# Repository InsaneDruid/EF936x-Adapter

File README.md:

# The EF936x-Adapter
Adapter for using an EF9367 instead of an EF9366/65, especially on the Low Speed Graphik graphics board

[Schematic](https://github.com/InsaneDruid/EF936x-Adapter/blob/main/ef936x_adapter.pdf "Schematic")  

[Bill of Materials](https://htmlpreview.github.io/?https://github.com/InsaneDruid/EF936x-Adapter/blob/main/bom/ef936x_adapter_bom.html "Bill of Materials")

## The License
This work is licensed under a Creative Commons Attribution-ShareAlike 4.0 International License.  
See https://creativecommons.org/licenses/by-sa/4.0/.

## The Credits
This work would not have been possible without the help from a bunch of amazing people from [VzEkC e. V. forums](https://forum.classic-computing.de/forum/ "forum.classic-computing.de"). Many thanks go out to:

* *AndyG* - for the images of the original hardware that were the inspiration and backbone for this project

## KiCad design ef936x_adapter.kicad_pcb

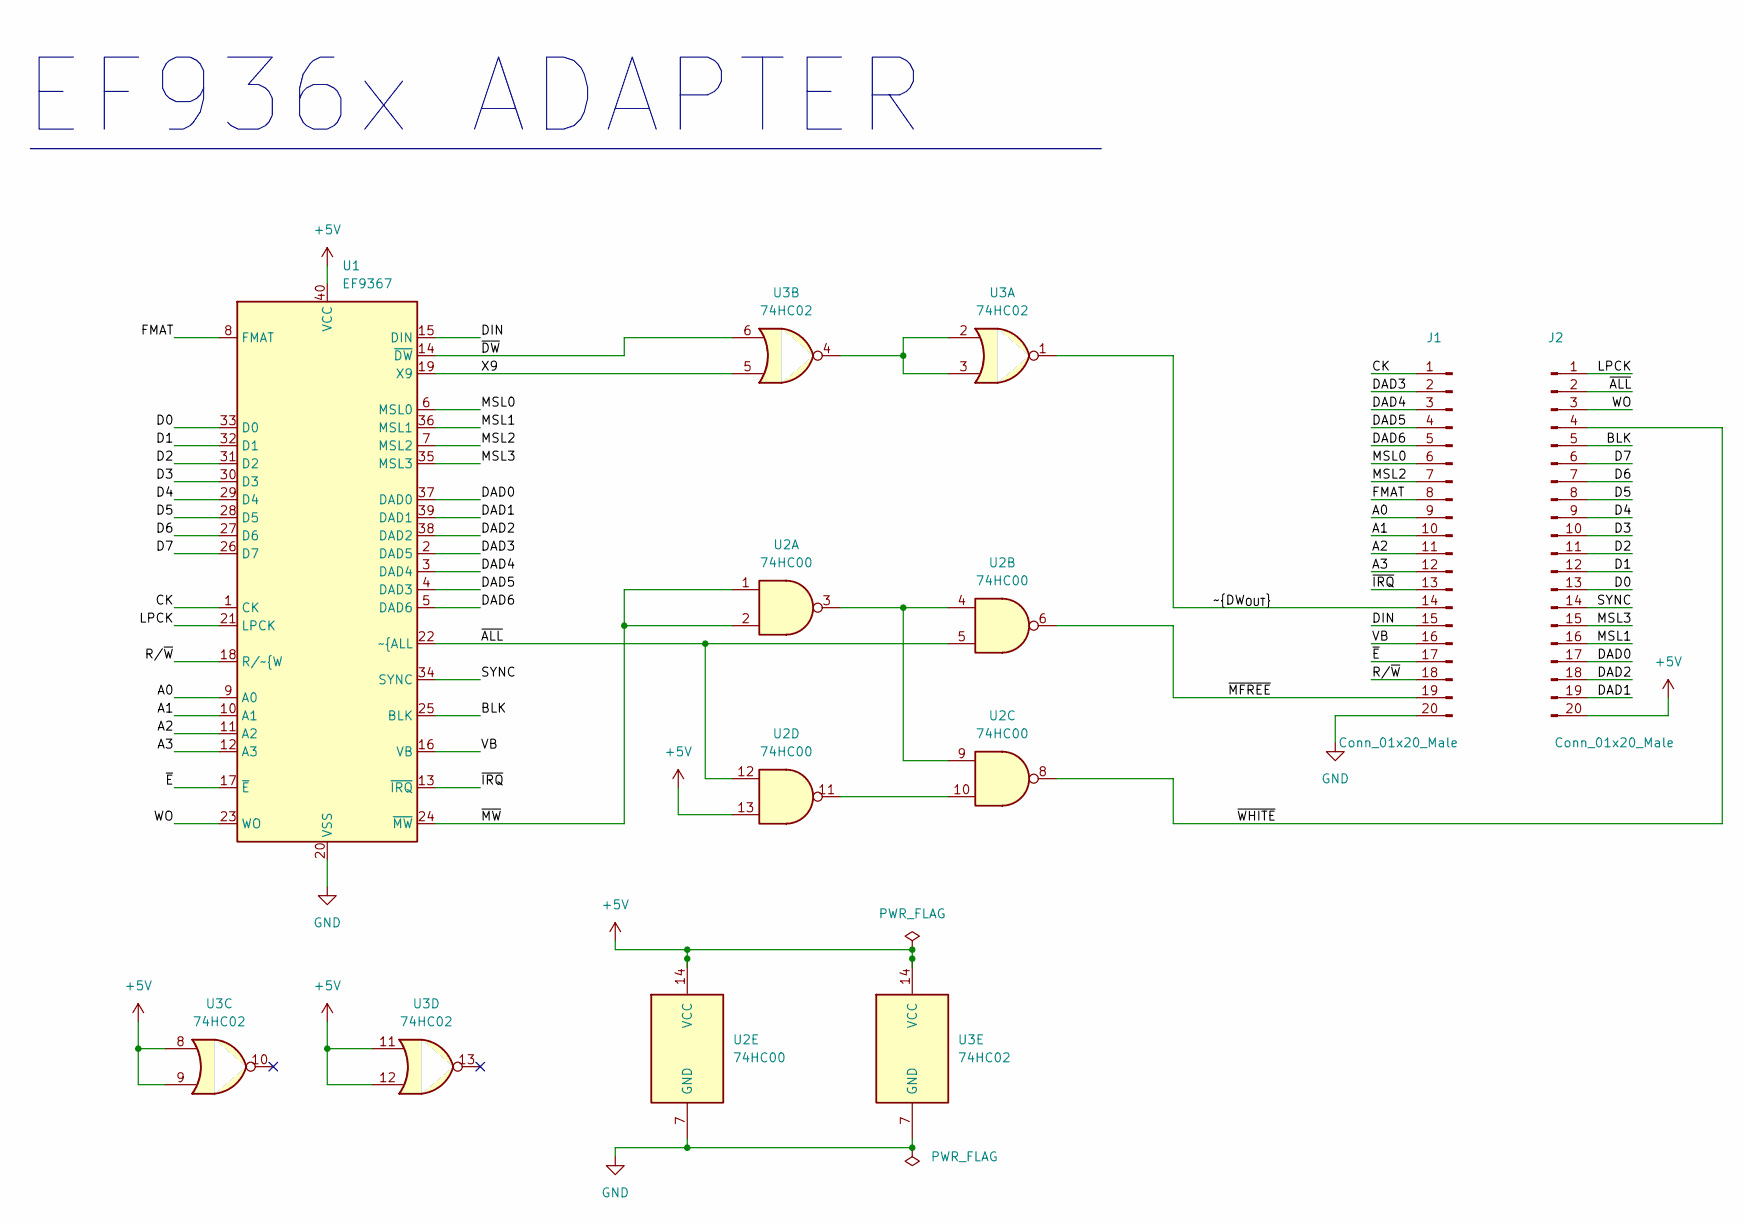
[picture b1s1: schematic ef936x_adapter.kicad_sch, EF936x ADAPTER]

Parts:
J1, J2: Conn_01x20_Male; PinHeader_1x20_P2.54mm_Vertical
U1: EF9367; DIP-40_W15.24mm_Socket
U2: 74HC00; DIP-14_W7.62mm
U3: 74HC02; DIP-14_W7.62mm

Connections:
+5V: J2.20, U1.40 (VCC), U2.13, U2.14 (VCC), U3.8, U3.9, U3.11, U3.12, U3.14 (VCC)
/A0: J1.9, U1.9 (A0)
/A1: J1.10, U1.10 (A1)
/A2: J1.11, U1.11 (A2)
/A3: J1.12, U1.12 (A3)
/BLK: J2.5, U1.25 (BLK)
/CK: J1.1, U1.1 (CK)
/D0: J2.13, U1.33 (D0)
/D1: J2.12, U1.32 (D1)
/D2: J2.11, U1.31 (D2)
/D3: J2.10, U1.30 (D3)
/D4: J2.9, U1.29 (D4)
/D5: J2.8, U1.28 (D5)
/D6: J2.7, U1.27 (D6)
/D7: J2.6, U1.26 (D7)
/DAD0: J2.17, U1.37 (DAD0)
/DAD1: J2.19, U1.39 (DAD1)
/DAD2: J2.18, U1.38 (DAD2)
/DAD3: J1.2, U1.2 (DAD5)
/DAD4: J1.3, U1.3 (DAD4)
/DAD5: J1.4, U1.4 (DAD3)
/DAD6: J1.5, U1.5 (DAD6)
/DIN: J1.15, U1.15 (DIN)
/FMAT: J1.8, U1.8 (FMAT)
/LPCK: J2.1, U1.21 (LPCK)
/MSL0: J1.6, U1.6 (MSL0)
/MSL1: J2.16, U1.36 (MSL1)
/MSL2: J1.7, U1.7 (MSL2)
/MSL3: J2.15, U1.35 (MSL3)
/R/~W: J1.18, U1.18 (R/~{W)
/SYNC: J2.14, U1.34 (SYNC)
/VB: J1.16, U1.16 (VB)
/WO: J2.3, U1.23 (WO)
/X9: U1.19 (X9), U3.5
/~ALL: J2.2, U1.22 (~{ALL), U2.5, U2.12
/~DW_{OUT}: J1.14, U3.1
/~DW: U1.14 (~DW), U3.6
/~E: J1.17, U1.17 (~E)
/~IRQ: J1.13, U1.13 (~IRQ)
/~MFREE: J1.19, U2.6
/~MW: U1.24 (~MW), U2.1, U2.2
/~WHITE: J2.4, U2.8
GND: J1.20, U1.20 (VSS), U2.7 (GND), U3.7 (GND)
unnamed: U2.3, U2.4, U2.9
unnamed: U2.10, U2.11
unnamed: U3.2, U3.3, U3.4

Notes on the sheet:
EF936x ADAPTER

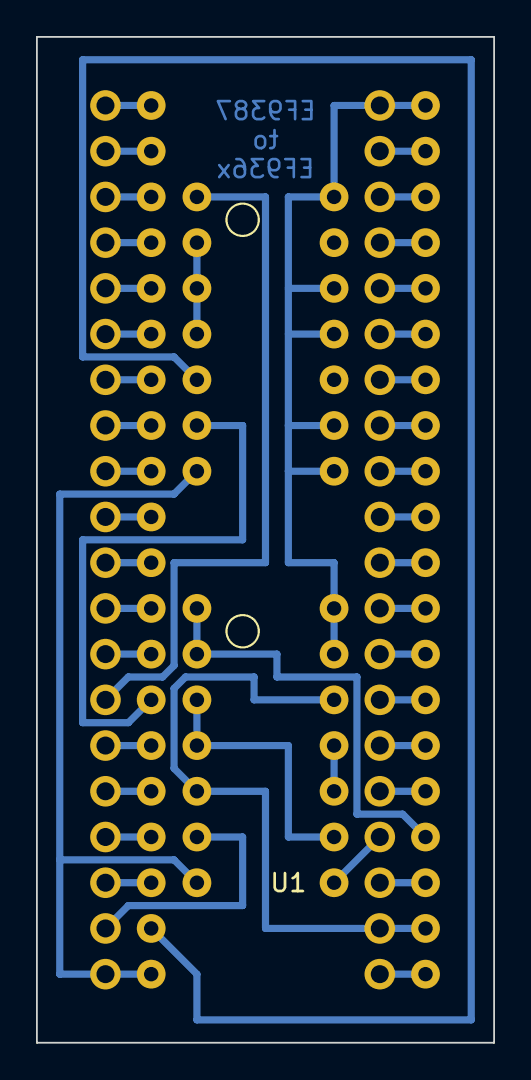
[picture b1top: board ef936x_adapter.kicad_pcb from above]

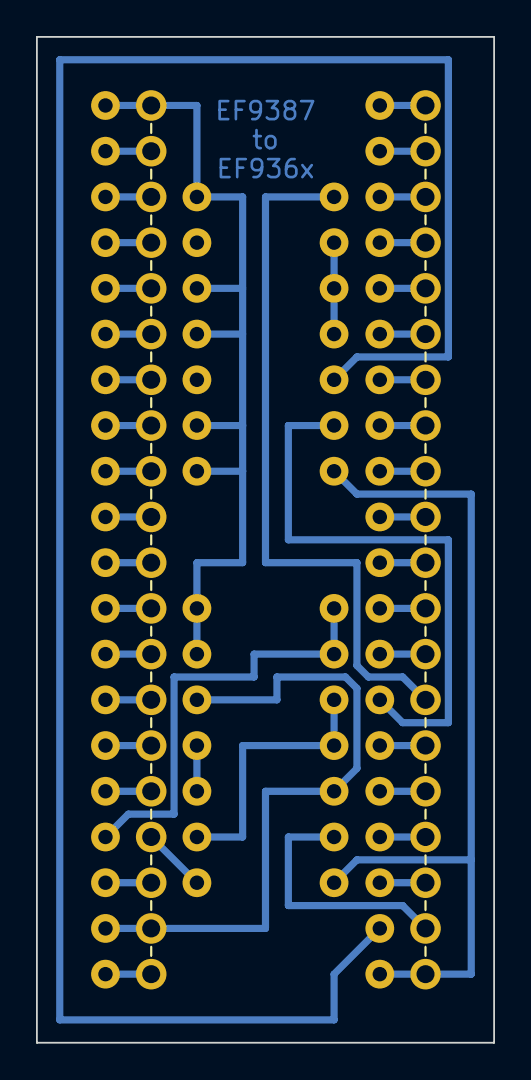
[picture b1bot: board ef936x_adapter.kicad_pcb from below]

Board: 2 copper layers, 25.4 x 55.9 mm, 5 parts (2 on the bottom side), 46 nets.

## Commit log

2023-02-23 KiCad7
    Update to KiCad7
2023-08-31 symbols and footprints rule checked
2024-02-16 kicad drawing sheet fixes
    fixed license links in drawing sheets to match board prints, readme and project
2024-02-20 Footprint fix
    -footprint of EF9367 set to be a socket
    -renamed schematic pdf file to be in line with other repos
2024-02-20 no soldermask version
    added a gerber containing masked out soldermaks for a vintage look
    (works with pcb manufacturers that have no option to turn of soldermask)

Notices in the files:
ef936x_adapter.kicad_pcb:
License: CC BY-SA 4.0
